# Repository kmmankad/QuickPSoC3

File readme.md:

QuickPSoC3 V2
--------------

This is a quick-to-make development envrionment for the Cypress PSoC3 Platform.It is intended for students,hobbyists or anyone who wants a PSoC3 platform to play with,without paying a ton of money for it.

The goal is to have a home-etchable,cheap to put together,USB capable PSoC3 environment running with the least of hassle.

To know more about the PSoC3 platform - http://www.cypress.com/?id=2232

This board:
-Uses the CY8C3866PVI-021/CY8C3246PVI-147 or any PSoC3 part in a 48pin SSOP package
-Has 26 GPIOs brought out to 0.1" headers.
-Uses the internal oscillator.
-Has a miniprog compatible header on the top right,for easy programming.
-Has a miniUSB connector,so can use a USB bootloader,for easier programming.
-Has extra long pads for soldering the PSoC,to make it easier for beginners to put together.
-The Mhz Crystal lines have not been routed out,but USB doesnt need an external crystal/resonator.
-Has smd passives of 0805 size,and the LEDs are 1206,but you can easily replace them with their through hole variants and get a fully through-hole board.
-Has an *Unregulated* voltage input which can be selected over USB's 5VDC.

I have successfully etched this using nothing but ordinary copier paper and a household iron,on some paper phenolic copper clad.So you dont require special techniques to etch it.

-kmmankad
http://kmmankad.blogspot.com

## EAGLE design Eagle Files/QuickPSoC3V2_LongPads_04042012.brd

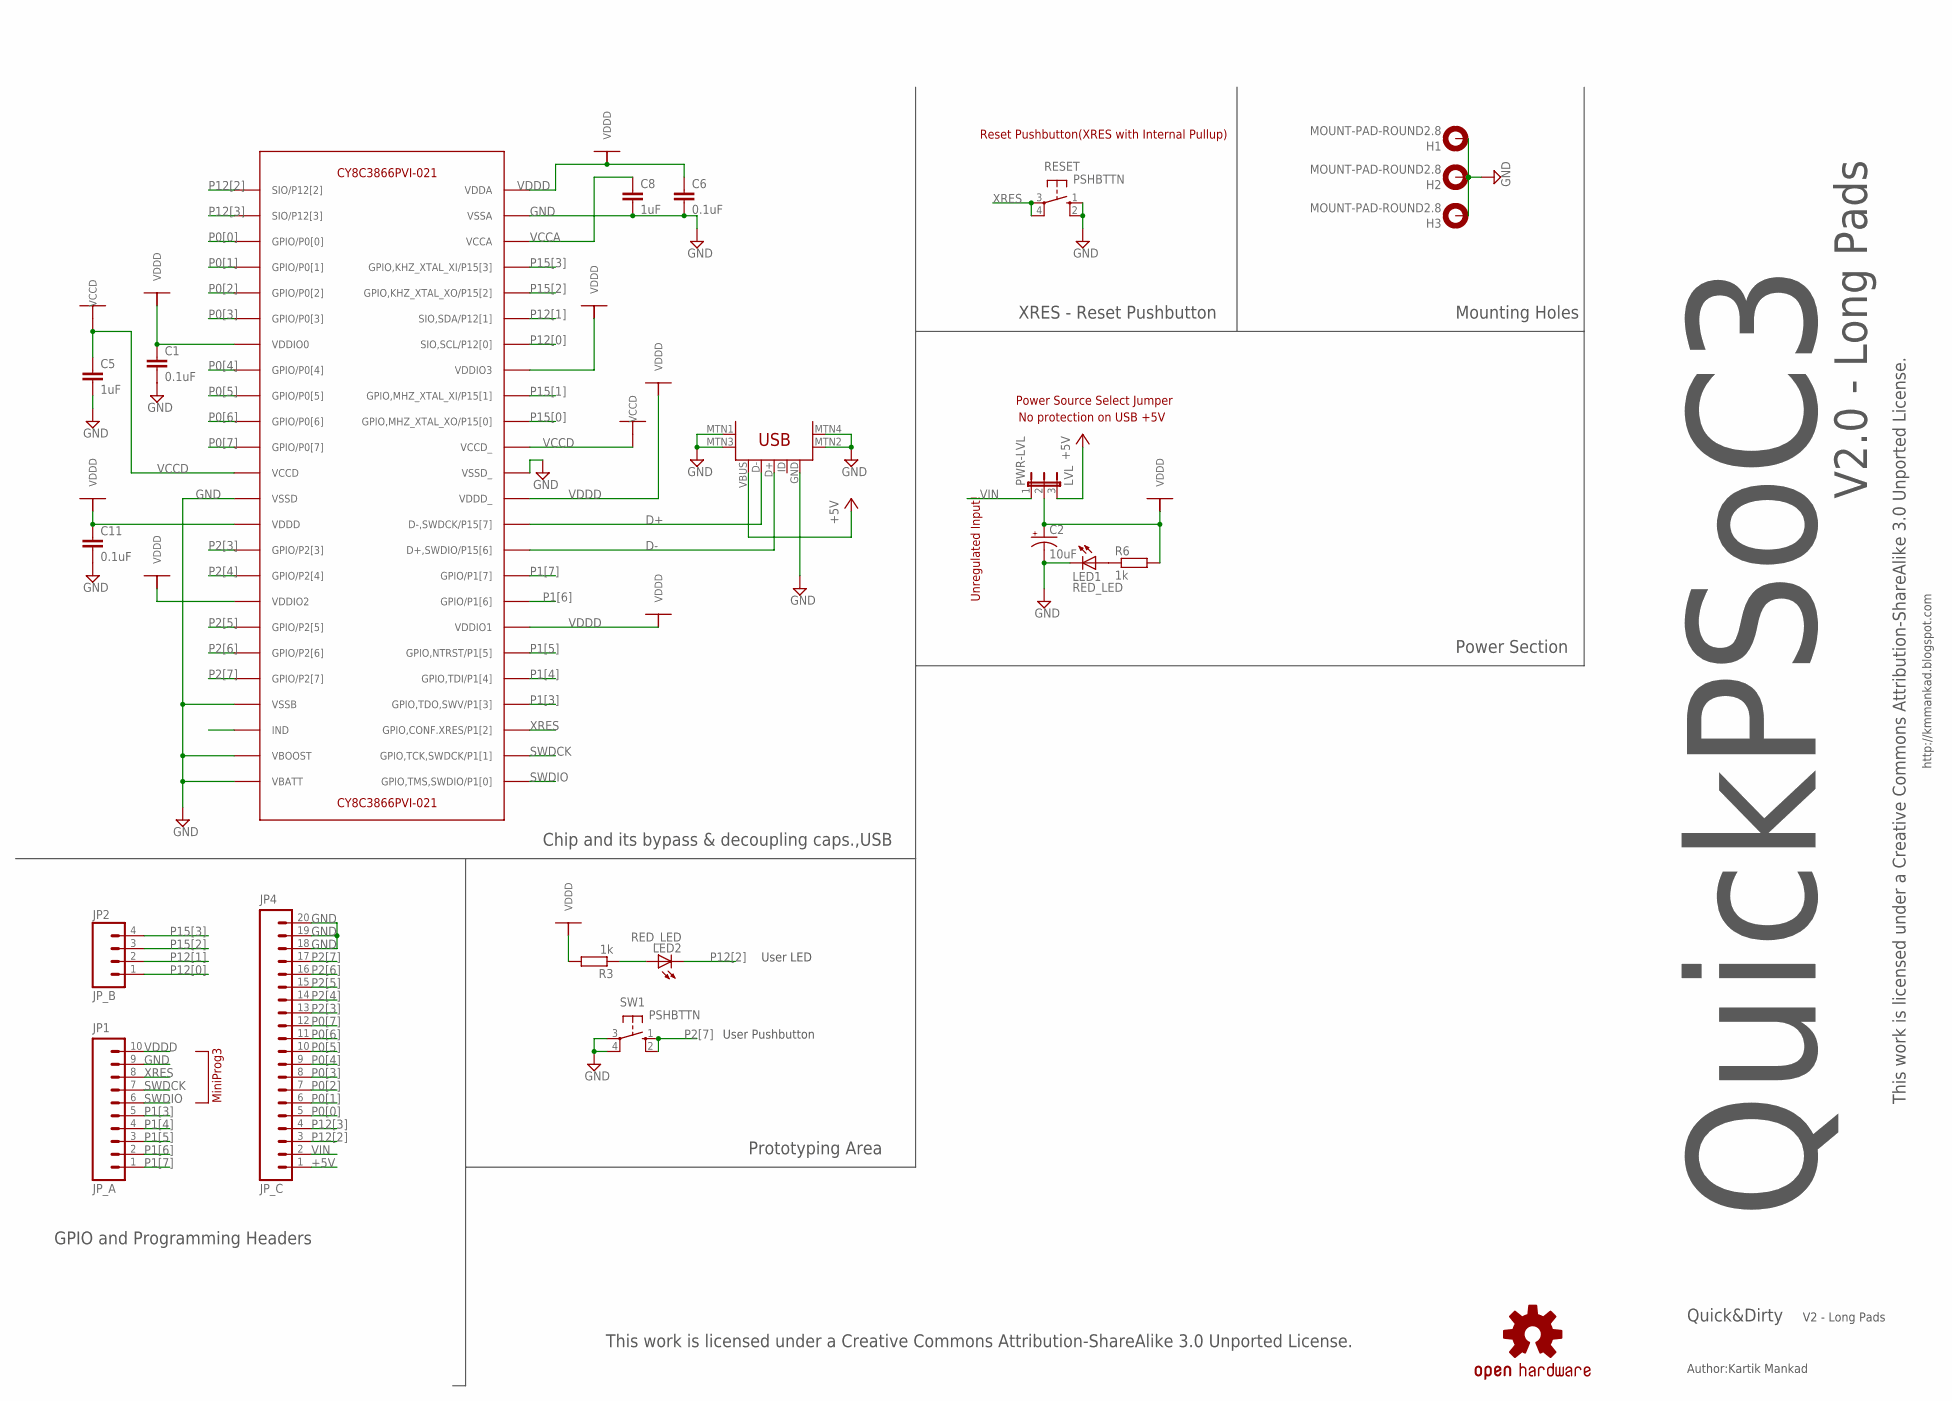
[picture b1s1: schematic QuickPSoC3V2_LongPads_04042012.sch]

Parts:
C1, C6, C11: 0.1uF; C0805K
C2: 10uF; CPOL-RADIAL-10UF-25V
C5, C8: 1uF; C0805K
H1, H2, H3: MOUNT-PAD-ROUND2.8; 2,8-PAD
JP1: JP_A; 1X10
JP2: JP_B; 1X04
JP4: JP_C; 1X20
LED1, LED2: RED_LED; LED-1206
PWR-LVL: LVL; JP2
R3, R6: 1k; M0805
RESET: PSHBTTN; B3F-10XX
SW1: PSHBTTN; B3F-10XX
U$1: CY8C3866PVI-021; SSOP48DL
U$2: OSHW-LOGOL; OSHW-LOGO-L
X1: USB-MINIB-5PIN; USB-MINIB

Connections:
+5V: JP4.1, PWR-LVL.3, X1.VBUS
D+: U$1.35 (D-,SWDCK/P15[7]), X1.D-
D-: U$1.34 (D+,SWDIO/P15[6]), X1.D+
GND: C1.2, C2.2 (-), C5.2, C6.2, C8.2, C11.2, H1.B2,8, H2.B2,8, H3.B2,8, JP1.9, JP4.18, JP4.19, JP4.20, LED1.C, RESET.1 (S), RESET.2 (S1), SW1.3, SW1.4 (P1), U$1.13 (VSSD), U$1.21 (VSSB), U$1.23 (VBOOST), U$1.24 (VBATT), U$1.37 (VSSD_), U$1.47 (VSSA), X1.GND, X1.MTN1 (MTN2), X1.MTN2 (MTN3), X1.MTN3 (MTN1), X1.MTN4
unnamed: LED1.A, R6.1
unnamed: LED2.A, R3.1
P0[0]: JP4.5, U$1.3 (GPIO/P0[0])
P0[1]: JP4.6, U$1.4 (GPIO/P0[1])
P0[2]: JP4.7, U$1.5 (GPIO/P0[2])
P0[3]: JP4.8, U$1.6 (GPIO/P0[3])
P0[4]: JP4.9, U$1.8 (GPIO/P0[4])
P0[5]: JP4.10, U$1.9 (GPIO/P0[5])
P0[6]: JP4.11, U$1.10 (GPIO/P0[6])
P0[7]: JP4.12, U$1.11 (GPIO/P0[7])
P1[3]: JP1.5, U$1.28 (GPIO,TDO,SWV/P1[3])
P1[4]: JP1.4, U$1.29 (GPIO,TDI/P1[4])
P1[5]: JP1.3, U$1.30 (GPIO,NTRST/P1[5])
P1[6]: JP1.2, U$1.32 (GPIO/P1[6])
P1[7]: JP1.1, U$1.33 (GPIO/P1[7])
P2[3]: JP4.13, U$1.15 (GPIO/P2[3])
P2[4]: JP4.14, U$1.16 (GPIO/P2[4])
P2[5]: JP4.15, U$1.18 (GPIO/P2[5])
P2[6]: JP4.16, U$1.19 (GPIO/P2[6])
P2[7]: JP4.17, SW1.1 (S), SW1.2 (S1), U$1.20 (GPIO/P2[7])
P12[0]: JP2.1, U$1.42 (SIO,SCL/P12[0])
P12[1]: JP2.2, U$1.43 (SIO,SDA/P12[1])
P12[2]: JP4.3, LED2.C, U$1.1 (SIO/P12[2])
P12[3]: JP4.4, U$1.2 (SIO/P12[3])
P15[0]: U$1.39 (GPIO,MHZ_XTAL_XO/P15[0])
P15[1]: U$1.40 (GPIO,MHZ_XTAL_XI/P15[1])
P15[2]: JP2.3, U$1.44 (GPIO,KHZ_XTAL_XO/P15[2])
P15[3]: JP2.4, U$1.45 (GPIO,KHZ_XTAL_XI/P15[3])
SWDCK: JP1.7, U$1.26 (GPIO,TCK,SWDCK/P1[1])
SWDIO: JP1.6, U$1.25 (GPIO,TMS,SWDIO/P1[0])
VCCA: C8.1, U$1.46 (VCCA)
VCCD: C5.1, U$1.12 (VCCD), U$1.38 (VCCD_)
VDDD: C1.1, C2.1 (+), C6.1, C11.1, JP1.10, PWR-LVL.2, R3.2, R6.2, U$1.7 (VDDIO0), U$1.14 (VDDD), U$1.17 (VDDIO2), U$1.31 (VDDIO1), U$1.36 (VDDD_), U$1.41 (VDDIO3), U$1.48 (VDDA)
VIN: JP4.2, PWR-LVL.1
XRES: JP1.8, RESET.3, RESET.4 (P1), U$1.27 (GPIO,CONF.XRES/P1[2])

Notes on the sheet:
Author:Kartik Mankad
This work is licensed under a Creative Commons Attribution-ShareAlike 3.0 Unported License.
Reset Pushbutton(XRES with Internal Pullup)
Quick&Dirty
MiniProg3
Unregulated Input!
Power Source Select Jumper
No protection on USB +5V
Chip and its bypass & decoupling caps.,USB
Power Section
XRES - Reset Pushbutton
Mounting Holes
Prototyping Area
GPIO and Programming Headers
User LED
User Pushbutton
QuickPSoC3
http://kmmankad.blogspot.com
V2 - Long Pads
V2.0 - Long Pads

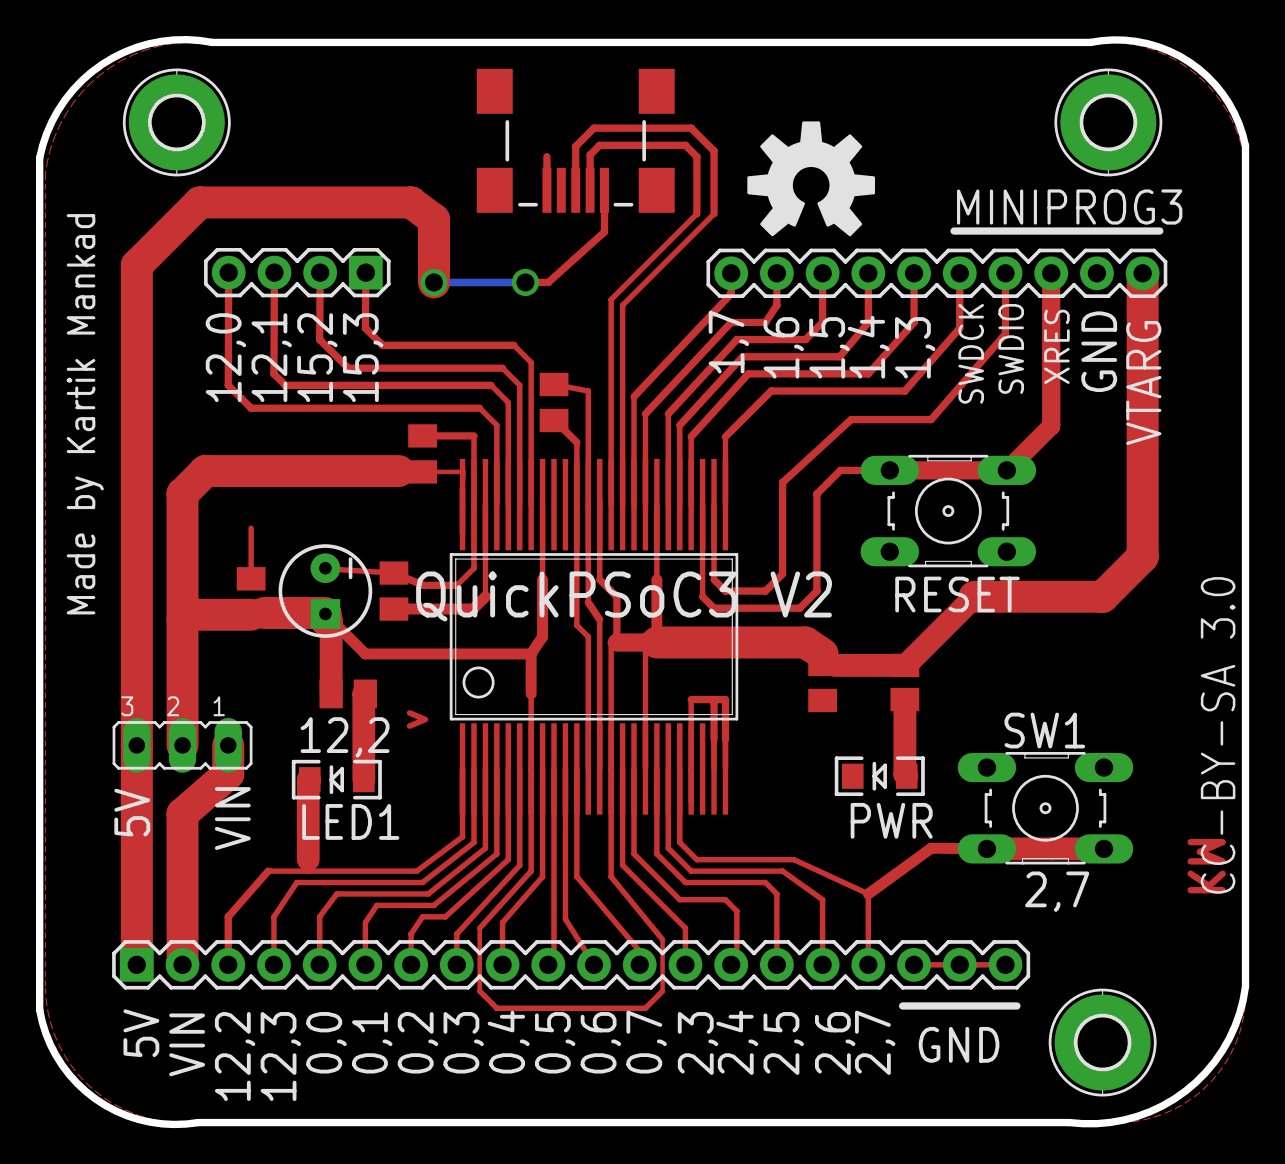
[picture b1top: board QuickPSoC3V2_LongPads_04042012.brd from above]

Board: 2 copper layers, 67.0 x 60.3 mm, 23 parts (0 on the bottom side), 37 nets.

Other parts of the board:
U$3: LOGO

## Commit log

2012-04-08 First commit.
2012-04-08 Added Readme
2012-04-08 Updated readme with basic info and blog address.
2012-04-08 updated basic info about the board
2012-04-08 Updated readme with license info
2012-04-08 renamed readme file.
2012-04-08 renamed readme.md to readme.txt
2012-04-08 fixed the formatting on the readme file.
2012-04-08 Changed directory structure,titled toner-transfer printouts.
2012-04-08 Fixed the silkscreen text for SW1.
2012-05-16 changed the git ignore file.
2012-06-15 Removed the 22ohm resistors on the USB lines,since it works just fine without them. Removed 10uF cap on USB +5V line. Added MiniProg3 insertion indication on silkscreen.
    Edited gitignore to ignore *.s#* and *.b#* files.
2012-06-19 Changed the Toner Transfer files. Edited the readme to reflect changes.
2012-06-19 Added Eagle version number to readme.txt

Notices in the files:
Eagle Files/QuickPSoC3V2_LongPads_04042012.brd:
CC-BY-SA 3.0
